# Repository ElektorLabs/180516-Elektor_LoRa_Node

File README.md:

# Elektor LoRa Node

## This is a Elektor LoRa Node based on a STM32F072

This is the hardware and software repository for the Elektor LoRa node.
This is open hardware under the CERN OHL v1.2, so feel free to grab your copy and have fun. 
Also this project is done with KiCad, so you can have a look at the files without software that costs a fortune.

Under the Hardware folder you will find (besides the project files) the PDF files for the board schematics.  

For more information and the motivation also to share the KiCad files with you have a look at https://www.elektormagazine.com/labs/lorawan-node-experimental-platform
If you are new to KiCad and would like to modify the PCB on your own, feel free, and if you need a good book to start with KiCad have a look at: https://www.elektor.com/kicad-like-a-pro

## Getting Started

Grab a copy of KiCad and download the repository, or just grab the schematics to get an idea of the board.

For the software grab a copy of the Arduino IDE and install the STM32 core support for Arduino ( https://github.com/stm32duino/Arduino_Core_STM32 )
You can use the excellent guide provided here : https://github.com/stm32duino/Arduino_Core_STM32#getting-started

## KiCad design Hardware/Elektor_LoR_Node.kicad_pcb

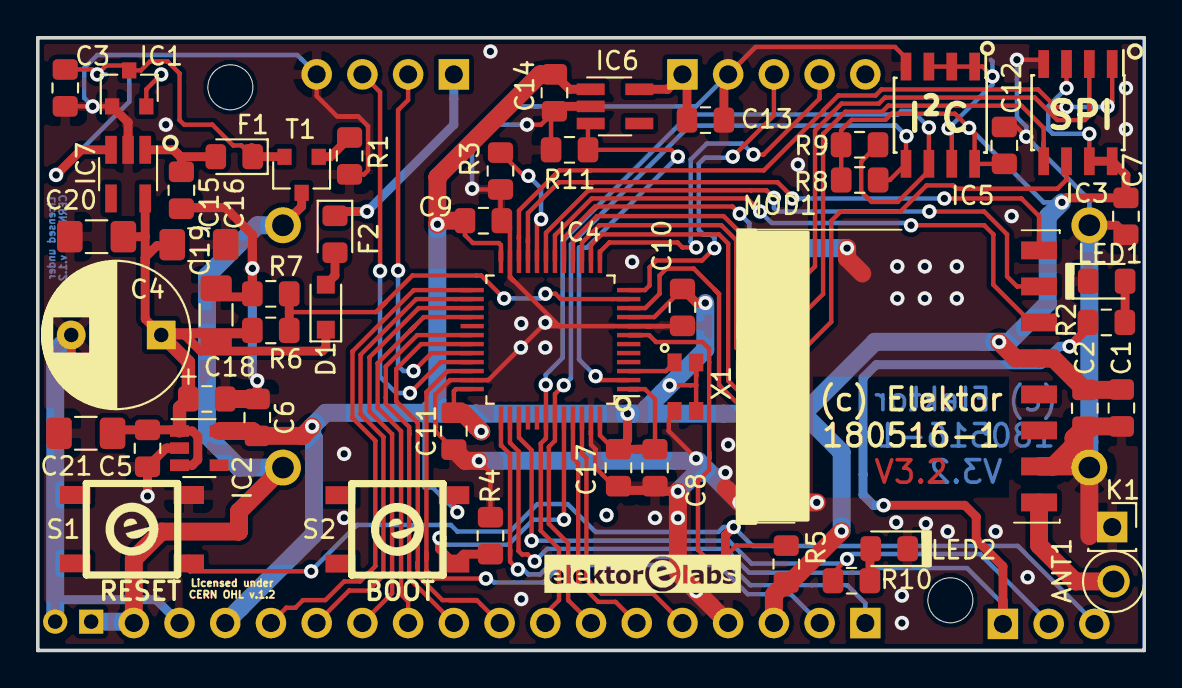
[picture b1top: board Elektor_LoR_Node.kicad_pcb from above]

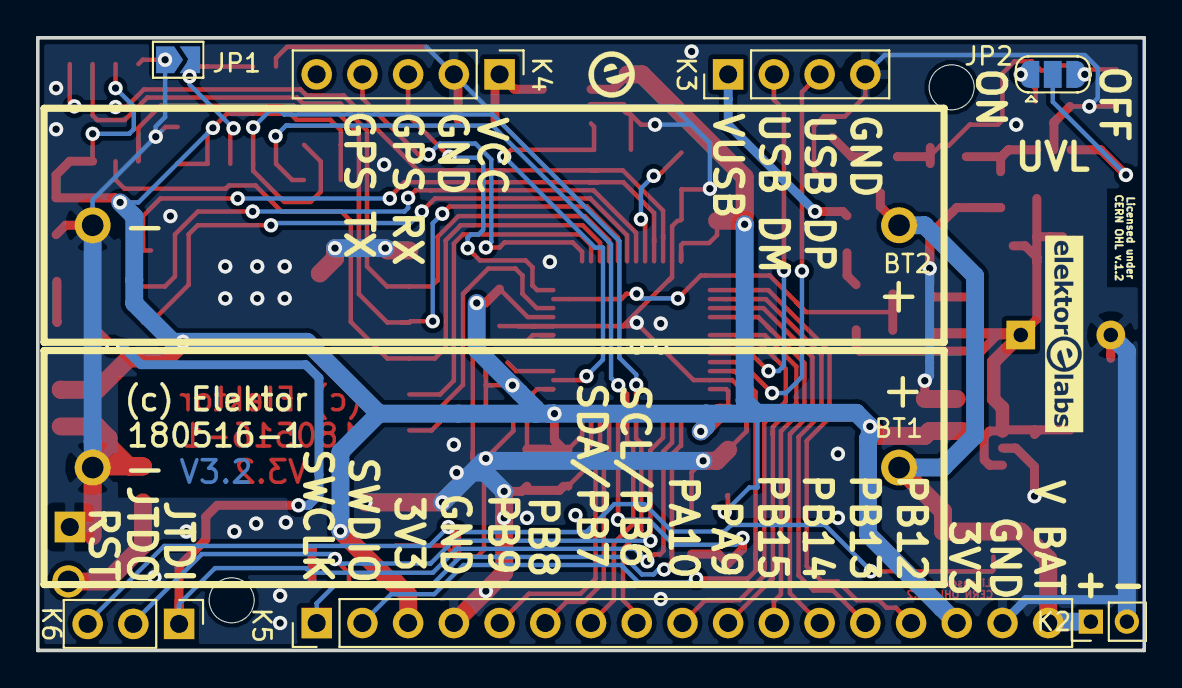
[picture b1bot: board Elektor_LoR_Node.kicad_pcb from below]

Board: 2 copper layers, 61.5 x 34.0 mm, 62 parts (9 on the bottom side), 49 nets.

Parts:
ANT1: Antenna; TestPoint_Plated_Hole_D2.0mm
BT1, BT2: multicomp pro AAA Battery Holder with PCB Pins; AAA_holder
C1, C5, C8, C14, C15: 4.7uF; C_0805_2012Metric_Pad1.15x1.40mm_HandSolder
C2, C3, C6, C7, C9, C10, C11, C12, C13, C17, C18: 100nF; C_0805_2012Metric_Pad1.15x1.40mm_HandSolder
C4: 470u; CP_Radial_D8.0mm_P5.00mm
C16, C19, C20, C21: 100uF; C_1206_3216Metric_Pad1.42x1.75mm_HandSolder
D1: PMEG3010EJ; D_SOD-323_HandSoldering
F1, F2: 0ZCK0050AF2E; D_0805_2012Metric_Pad1.15x1.40mm_HandSolder
H1, H2: MountingHole; MountingHole_2.5mm
IC1: TLV809K33; SOT-23
IC2: TLV75533PDBV; SOT-23-5
IC3: AT25SF081-SSHD-X; SOIC-8_3.9x4.9mm_P1.27mm
IC4: STM32F072C8Tx; LQFP-48_7x7mm_P0.5mm
IC5: ATECC608A; SOIC-8_3.9x4.9mm_P1.27mm
IC6, IC7: MAX40200; SOT-23-5_HandSoldering
JP1: SolderJumper_2_Open; SolderJumper-2_P1.3mm_Open_TrianglePad1.0x1.5mm
JP2: SolderJumper_3_Open; SolderJumper-3_P1.3mm_Open_RoundedPad1.0x1.5mm
K1: Conn_01x01_Female; PinSocket_1x01_P2.54mm_Vertical
K2: Conn_01x02_Male; PinHeader_1x02_P2.00mm_Vertical
K3: Conn_01x04_Male; PinHeader_1x04_P2.54mm_Vertical
K4: Conn_01x05_Female; PinHeader_1x05_P2.54mm_Vertical
K5: Conn_01x17_Female; PinHeader_1x17_P2.54mm_Vertical
K6: Conn_01x03_Male; PinHeader_1x03_P2.54mm_Vertical
LED1: LED_RED; LED_0805_2012Metric_Pad1.15x1.40mm_HandSolder
LED2: LED_GREEN; LED_0805_2012Metric_Pad1.15x1.40mm_HandSolder
MOD1: RFM95W-868S2; RFM9xW-Compact
R1: 100k; R_0805_2012Metric_Pad1.15x1.40mm_HandSolder
R2, R10: 680R; R_0805_2012Metric_Pad1.15x1.40mm_HandSolder
R3, R8, R9: 4k7; R_0805_2012Metric_Pad1.15x1.40mm_HandSolder
R4, R5, R11: 10k; R_0805_2012Metric_Pad1.15x1.40mm_HandSolder
R6, R7: 150k; R_0805_2012Metric_Pad1.15x1.40mm_HandSolder
S1: Reset; SMT switch TL3342
S2: Boot; SMT switch TL3342
T1: SI2347DS; SOT-23
X1: ASH7KW; ABRACON-ASH7KW

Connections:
3V3: C1.2, C2.1, C6.1, C7.2, C8.1, C9.1, C10.1, C11.1, C12.2, C14.1, C17.1, IC2.5, IC3.3, IC3.7, IC3.8, IC4.1, IC4.9, IC4.24, IC4.36, IC4.48, IC5.8, IC6.1, K5.3, K5.15, MOD1.13, R5.2, R8.1, R9.1, S2.1, X1.3, X1.4
CAN_RX: IC4.45, K5.6
CAN_TX: IC4.46, K5.5
GND: BT1.2, BT2.2, C1.1, C2.2, C3.2, C4.2, C5.2, C6.2, C7.1, C8.2, C9.2, C10.2, C11.2, C12.1, C13.1, C14.2, C15.2, C16.2, C17.2, C18.2, C19.2, C20.2, C21.2, IC1.1, IC2.2, IC3.4, IC4.8, IC4.23, IC4.35, IC4.47, IC5.4, IC6.2, IC7.2, JP1.1, K1.1, K2.2, K3.4, K4.2, K5.4, K5.16, LED1.1, LED2.1, MOD1.1, MOD1.8, MOD1.10, R1.2, R3.2, R4.2, R7.2, R11.2, S1.1, X1.2
GPS_ACTIVE_ON: IC4.2, IC6.3, R11.1
GPS_RXD: IC4.12, K4.3
GPS_TXD: IC4.13, K4.4
I2C_SCL: IC4.42, IC5.6, K5.8, R8.2
I2C_SDA: IC4.43, IC5.5, K5.7, R9.2
JTDI: IC4.38, K6.1, R2.2
JTDO: IC4.39, K6.2, R10.1
unnamed: ANT1.1, MOD1.9
unnamed: C3.1, F1.1, IC1.3, JP2.3, T1.2
unnamed: C13.2, IC6.5, K4.1
unnamed: C15.1, F1.2, IC7.1
unnamed: D1.2, F2.2
unnamed: IC1.2, JP2.1
unnamed: IC4.3, X1.1
unnamed: IC4.11, R6.2, R7.1
unnamed: IC4.20, R3.1
unnamed: IC4.44, R4.1, S2.2
unnamed: IC5.1, IC5.2, IC5.3, IC5.7, JP1.2
unnamed: IC7.3, JP2.2
unnamed: LED1.2, R2.1
unnamed: LED2.2, R10.2
unnamed: R1.1, T1.1
RFM95_DIO0: IC4.21, MOD1.16
RFM95_DIO1: IC4.19, MOD1.15
RFM95_DIO2: IC4.18, MOD1.14
RFM95_MISO: IC3.2, IC4.16, MOD1.2
RFM95_MOSI: IC3.5, IC4.17, MOD1.3
RFM95_RESET: IC4.10, MOD1.6
RFM95_SCK: IC3.6, IC4.15, MOD1.4
SPI_NOR_NCS: IC3.1, IC4.22
SWCLK: IC4.37, K5.1
SWDIO: IC4.34, K5.2
UNUSED_00: IC4.25, K5.14
UNUSED_01: IC4.26, K5.13
UNUSED_02: IC4.27, K5.12
UNUSED_03: IC4.28, K5.11
UNUSED_04: IC4.30, K5.10
UNUSED_05: IC4.31, K5.9
USBDM: IC4.32, K3.2
USBDP: IC4.33, K3.3
VBAT: BT1.1, BT2.1, K2.1, K5.17, T1.3
VSupply: C4.1, C5.1, C16.1, C18.1, C19.1, C20.1, C21.1, D1.1, IC2.1, IC2.3, IC7.5, R6.1
VUSB: F2.1, K3.1
~RFM95_CS: IC4.14, MOD1.5
~RST: IC4.7, K6.3, R5.1, S1.2

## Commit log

2019-11-08 Version 3.1
    Small changes towards V3.2 already done for cleanup and bugfixing
2019-12-02 Files for Version 3.2
    Fixed library problems within the project
2019-12-02 Fixed some typos
2022-06-28 Update README.md
    Spelling and grammar.

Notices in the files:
Hardware/Elektor_LoR_Node.kicad_pcb:
Licensed under
CERN OHL v.1.2
